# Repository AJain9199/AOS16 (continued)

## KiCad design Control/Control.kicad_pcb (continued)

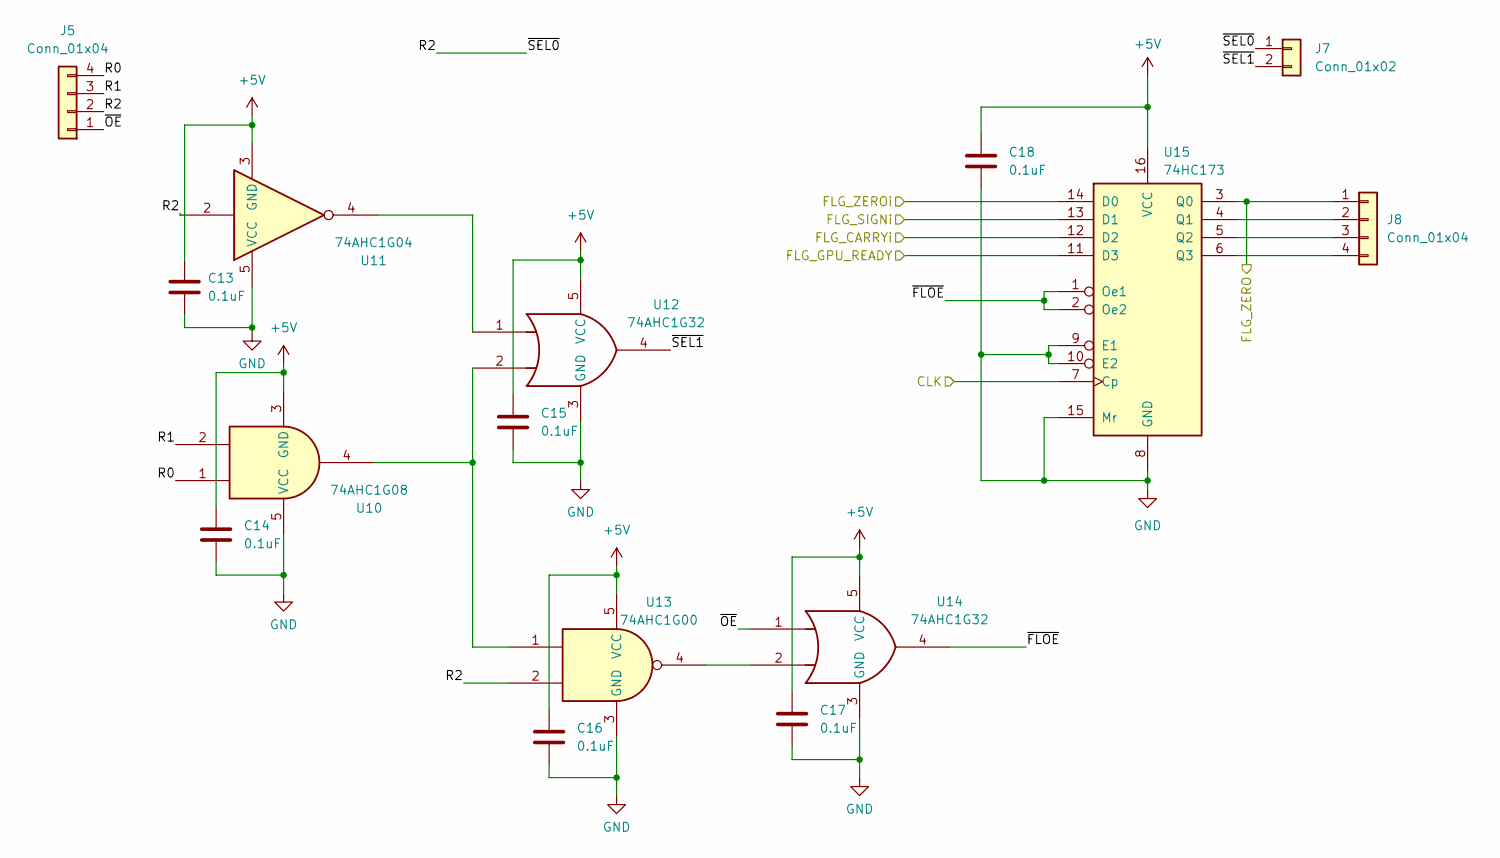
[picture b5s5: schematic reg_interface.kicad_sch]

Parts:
C13, C14, C15, C16, C17, C18: 0.1uF; C_0603_1608Metric
J5, J8: Conn_01x04; PinSocket_1x04_P2.54mm_Vertical
J7: Conn_01x02; PinHeader_1x02_P2.54mm_Vertical
U10: 74AHC1G08; SOT-23-5
U11: 74AHC1G04; SOT-23-5
U12, U14: 74AHC1G32; SOT-23-5
U13: 74AHC1G00; SOT-23-5
U15: 74HC173; SOIC-16_3.9x9.9mm_P1.27mm

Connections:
+5V: C13.1, C14.1, C15.1, C16.1, C17.1, C18.1, U10.3 (GND), U11.3 (GND), U12.5 (VCC), U13.5 (VCC), U14.5 (VCC), U15.16 (VCC); also elsewhere on the board
/ALU interface/FLG_CARRYo: U15.12 (D2); also elsewhere on the board
/ALU interface/FLG_SIGNo: U15.13 (D1); also elsewhere on the board
/ALU interface/FLG_ZEROo: U15.14 (D0); also elsewhere on the board
/CLK: U15.7 (Cp); also elsewhere on the board
/FLG_ZERO: J8.1, U15.3 (Q0); also elsewhere on the board
/register interface/FLG_GPU_READY: U15.11 (D3); also elsewhere on the board
/register interface/R0: J5.4, U10.1
/register interface/R1: J5.3, U10.2
/register interface/R2: J5.2, J7.1, U11.2, U13.2
/register interface/~FLOE: U14.4, U15.1 (Oe1), U15.2 (Oe2)
/register interface/~OE: J5.1, U14.1
/register interface/~SEL1: J7.2, U12.4
GND: C13.2, C14.2, C15.2, C16.2, C17.2, C18.2, U10.5 (VCC), U11.5 (VCC), U12.3 (GND), U13.3 (GND), U14.3 (GND), U15.8 (GND), U15.9 (E1), U15.10 (E2), U15.15 (Mr); also elsewhere on the board
unnamed: J8.2, U15.4 (Q1)
unnamed: J8.3, U15.5 (Q2)
unnamed: J8.4, U15.6 (Q3)
unnamed: U10.4, U12.2, U13.1
unnamed: U11.4, U12.1
unnamed: U13.4, U14.2

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
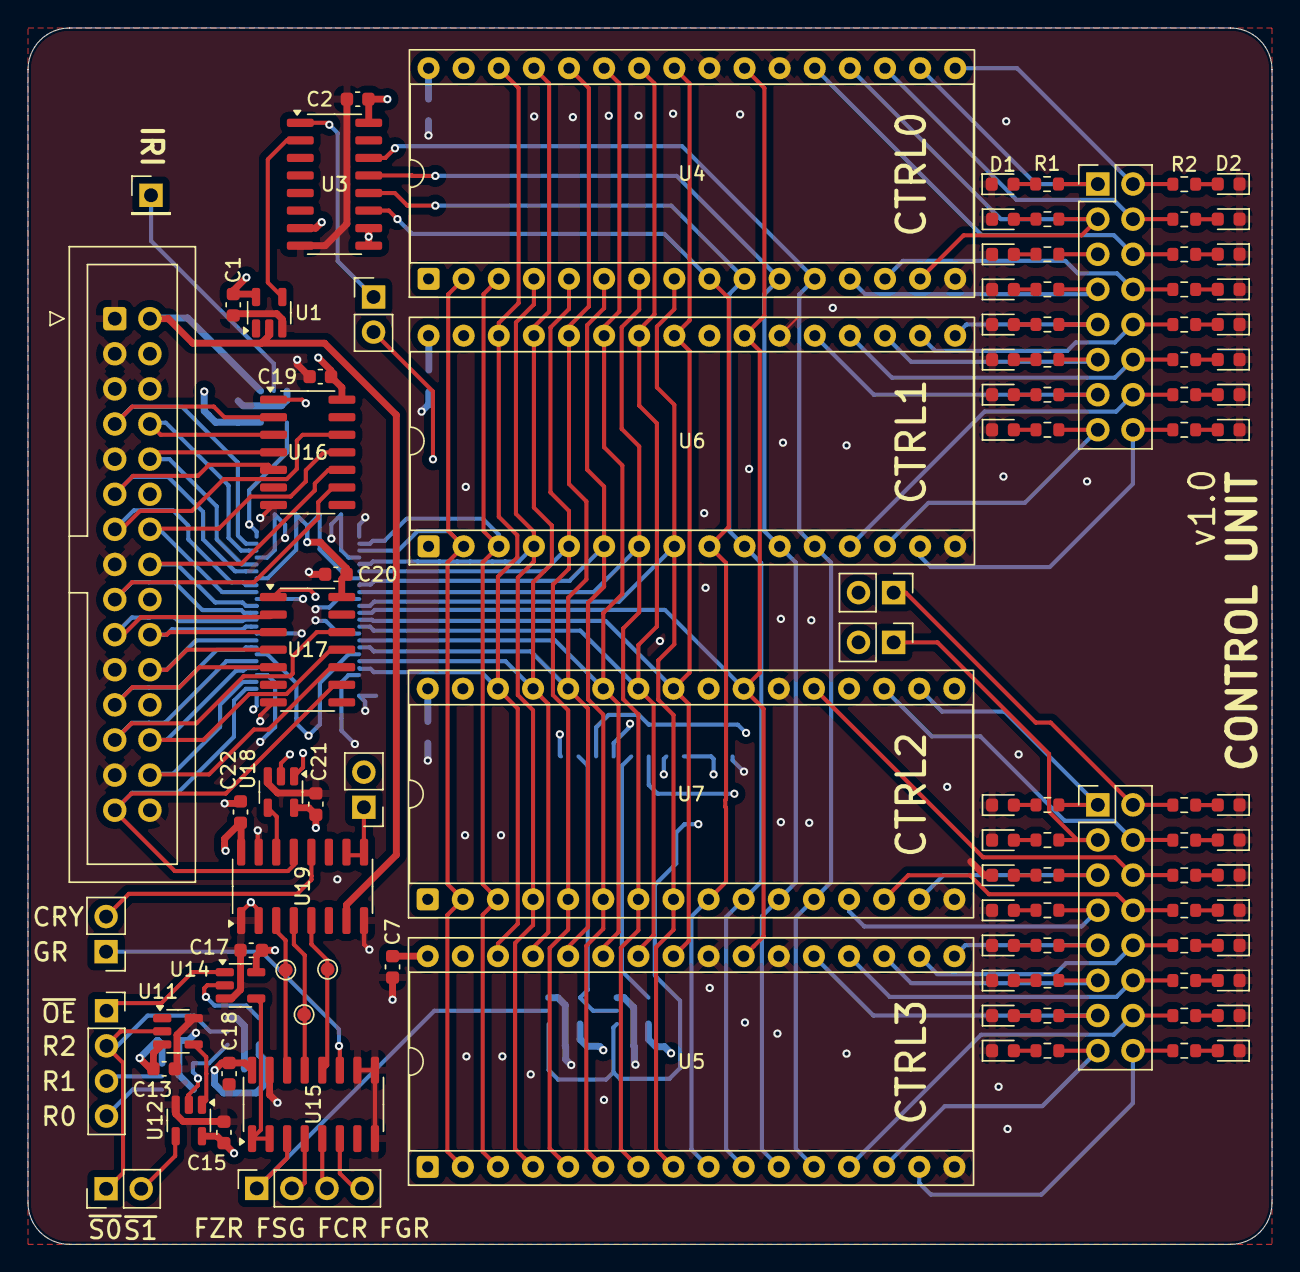
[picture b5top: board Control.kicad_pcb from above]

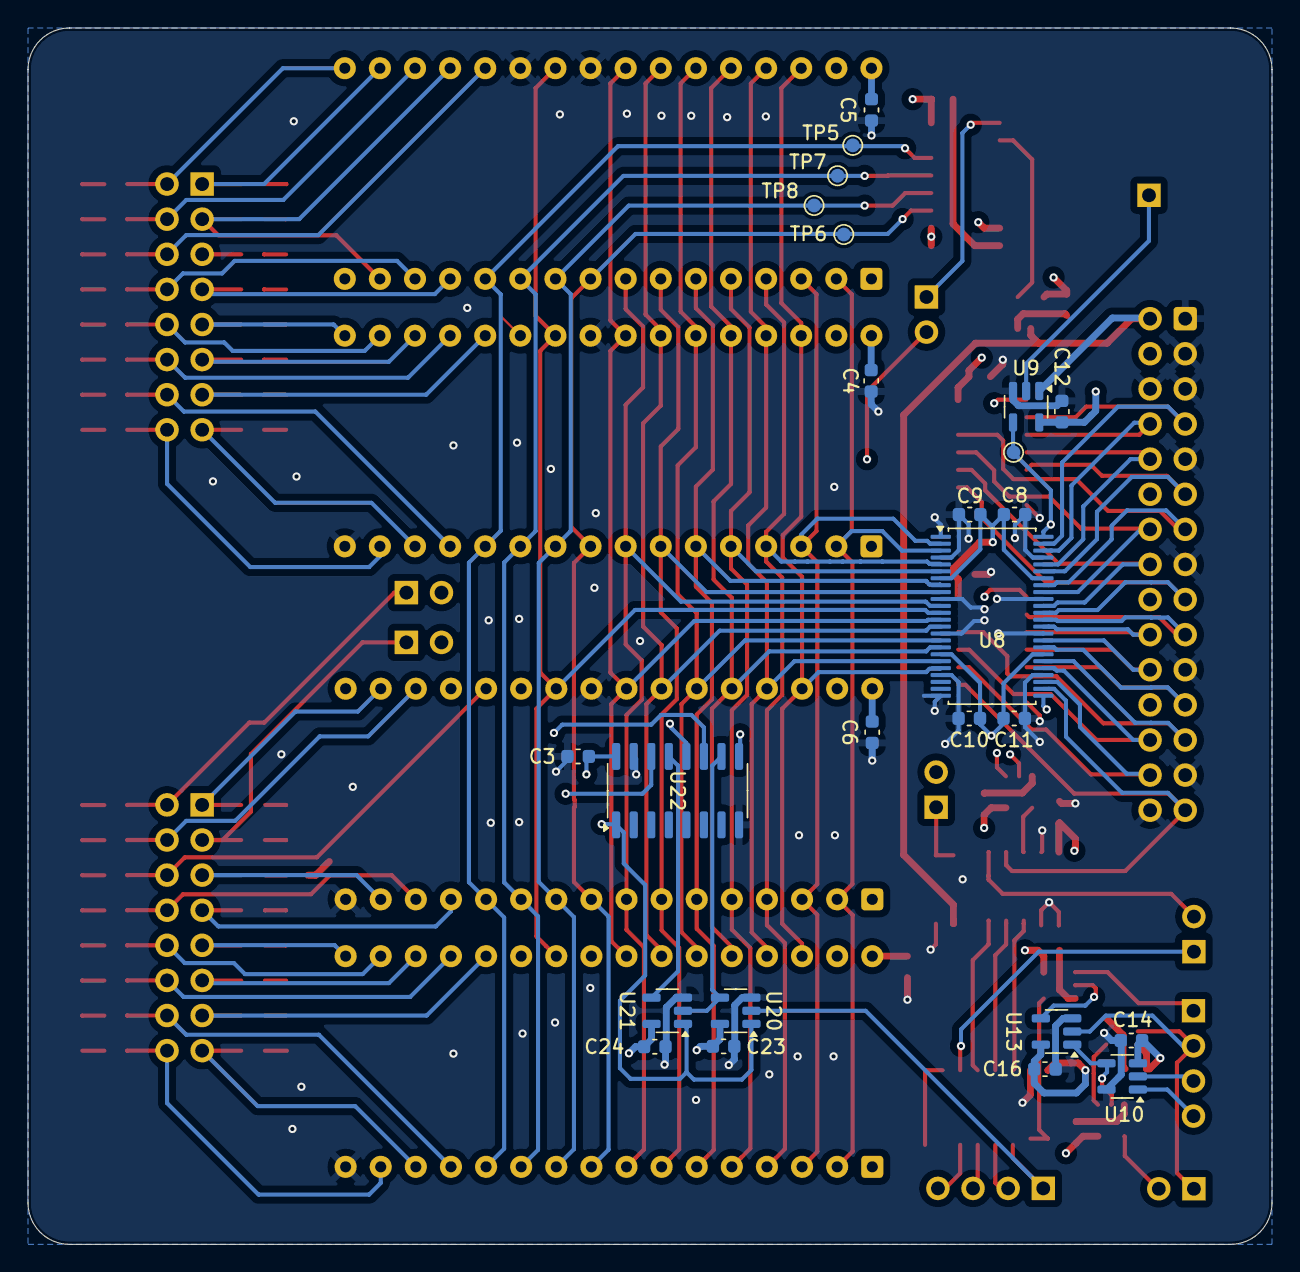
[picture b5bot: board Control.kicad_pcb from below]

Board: 4 copper layers, 90.0 x 88.0 mm, 129 parts (25 on the bottom side), 133 nets.

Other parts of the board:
C8, C9, C10, C11: 0.01uF; C_0603_1608Metric
C12: 0.1uF; C_0603_1608Metric
J3: Conn_02x15_Odd_Even; IDC-Header_2x15_P2.54mm_Vertical
TP1: TestPoint; TestPoint_Pad_D1.0mm
U8: SN74AHCT16374DGGR; TSSOP-48_6.1x12.5mm_P0.5mm
U9: 74AHC1G08; SOT-23-5

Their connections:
+5V: C8.1, C9.1, C10.1, C11.1, C12.1, J3.4, U8.7 (VCC_1), U8.18 (VCC_2), U8.31 (VCC), U8.42 (VCC_4), U9.5 (VCC); also elsewhere on the board
/ALU interface/BUS0: J3.7, U8.47 (1D1); also elsewhere on the board
/ALU interface/BUS1: J3.8, U8.46 (1D2); also elsewhere on the board
/ALU interface/BUS2: J3.10, U8.44 (1D3); also elsewhere on the board
/ALU interface/BUS3: J3.11, U8.43 (1D4); also elsewhere on the board
/ALU interface/BUS4: J3.13, U8.41 (1D5); also elsewhere on the board
/ALU interface/BUS5: J3.14, U8.40 (1D6); also elsewhere on the board
/ALU interface/BUS6: J3.16, U8.38 (1D7); also elsewhere on the board
/ALU interface/BUS7: J3.17, U8.37 (1D8); also elsewhere on the board
/ALU interface/BUS8: J3.19, U8.36 (2D1); also elsewhere on the board
/ALU interface/BUS9: J3.20, U8.35 (2D2); also elsewhere on the board
/ALU interface/BUS10: J3.22, U8.33 (2D3); also elsewhere on the board
/ALU interface/BUS11: J3.23, U8.32 (2D4); also elsewhere on the board
/ALU interface/BUS12: J3.25, U8.30 (2D5); also elsewhere on the board
/ALU interface/BUS13: J3.26, U8.29 (2D6); also elsewhere on the board
/ALU interface/BUS14: J3.28, U8.27 (2D7); also elsewhere on the board
/ALU interface/BUS15: J3.29, U8.26 (2D8); also elsewhere on the board
/CLK: J3.2, U9.1; also elsewhere on the board
/reg16/DOUT0: U8.2 (1Q1); also elsewhere on the board
/reg16/DOUT1: U8.3 (1Q2); also elsewhere on the board
/reg16/DOUT2: U8.5 (1Q3); also elsewhere on the board
/reg16/DOUT3: U8.6 (1Q4); also elsewhere on the board
/reg16/DOUT4: U8.8 (1Q5); also elsewhere on the board
/reg16/DOUT5: U8.9 (1Q6); also elsewhere on the board
/reg16/DOUT6: U8.11 (1Q7); also elsewhere on the board
/reg16/DOUT7: U8.12 (1Q8); also elsewhere on the board
/reg16/DOUT8: U8.13 (2Q1); also elsewhere on the board
/reg16/DOUT9: U8.14 (2Q2); also elsewhere on the board
/reg16/DOUT10: U8.16 (2Q3); also elsewhere on the board
/reg16/DOUT11: U8.17 (2Q4); also elsewhere on the board
/reg16/DOUT12: U8.19 (2Q5); also elsewhere on the board
/reg16/DOUT13: U8.20 (2Q6); also elsewhere on the board
/reg16/WE: U9.2; also elsewhere on the board
GND: C8.2, C9.2, C10.2, C11.2, C12.2, J3.1, J3.3, J3.5, J3.6, J3.9, J3.12, J3.15, J3.18, J3.21, J3.24, J3.27, J3.30, U8.1 (1~OE), U8.4 (GND_1), U8.10 (GND_2), U8.15 (GND_3), U8.21 (GND_4), U8.24 (2~OE), U8.28 (GND), U8.34 (GND_6), U8.39 (GND_7), U8.45 (GND_8), U9.3 (GND); also elsewhere on the board
unnamed: TP1.1, U8.25 (2CLK), U8.48 (1CLK), U9.4

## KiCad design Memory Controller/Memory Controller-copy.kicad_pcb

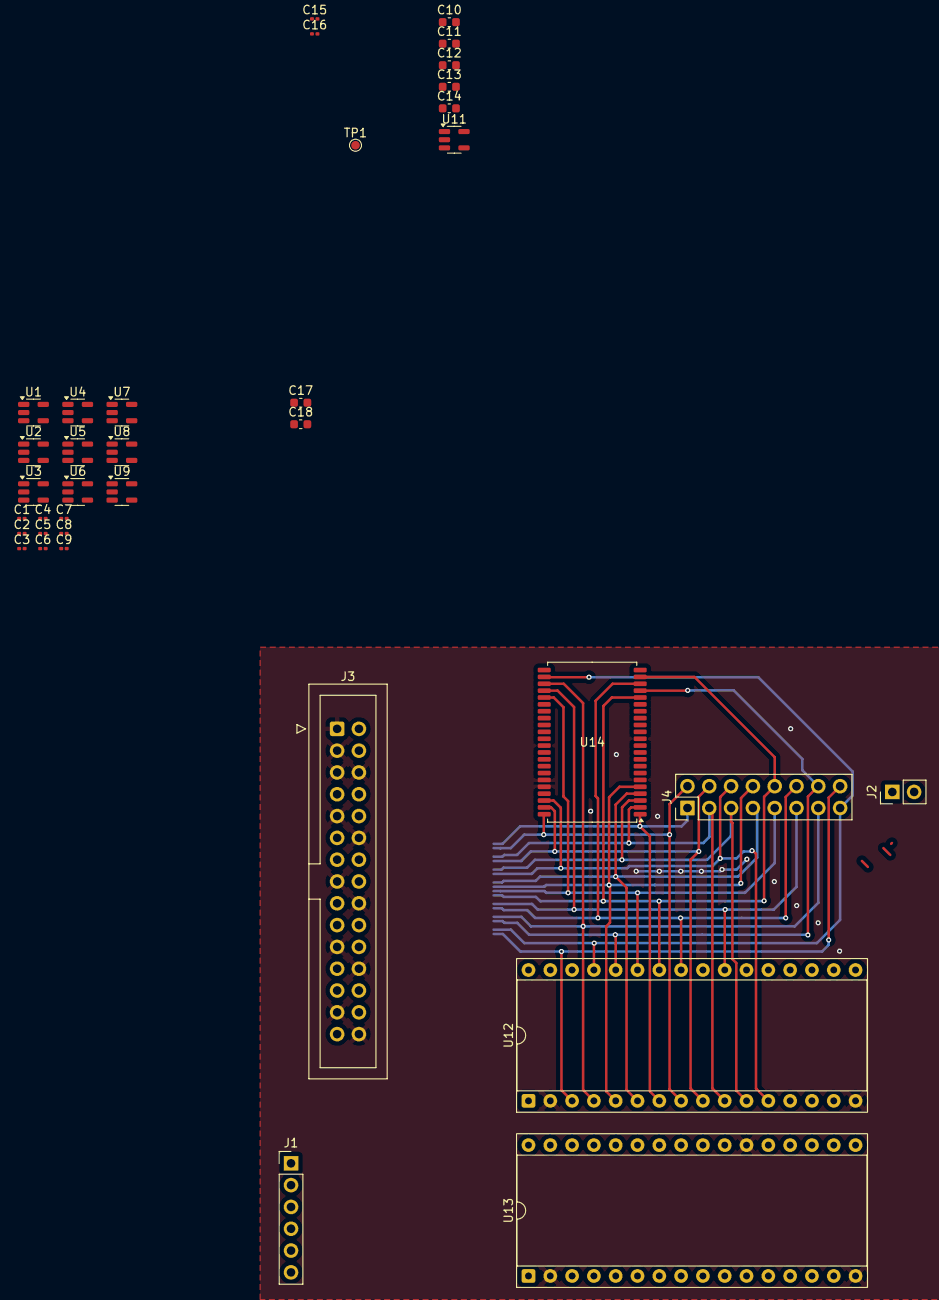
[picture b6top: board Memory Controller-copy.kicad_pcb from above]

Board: 2 copper layers, 37 parts (1 on the bottom side), 49 nets.

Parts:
C1, C2, C3, C4, C5, C6, C7, C8, C9, C15, C16: C; C_0201_0603Metric
C10, C11, C12, C13: 0.01uF; C_0603_1608Metric
C14, C17, C18: 0.1uF; C_0603_1608Metric
J1: Conn_01x06; PinHeader_1x06_P2.54mm_Vertical
J2: Conn_01x02; PinHeader_1x02_P2.54mm_Vertical
J3: Conn_02x15_Odd_Even; IDC-Header_2x15_P2.54mm_Vertical
J4: Conn_02x08_Top_Bottom; PinHeader_2x08_P2.54mm_Vertical
TP1: TestPoint; TestPoint_Pad_D1.0mm
U1, U3, U4, U5, U7, U8, U9: 74AHC1G32; SOT-23-5
U2, U6: 74AHC1G04; SOT-23-5
U10: SN74AHCT16374DGGR; TSSOP-48_6.1x12.5mm_P0.5mm
U11: 74AHC1G08; SOT-23-5
U12, U13: SST39SF010; DIP-32_W15.24mm_Socket
U14: 71016S12PHG8; TSOP-II-44_10.16x18.41mm_P0.8mm

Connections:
+5V: C1.1, C2.1, C3.1, C4.1, C5.1, C6.1, C7.1, C8.1, C9.1, C10.1, C11.1, C12.1, C13.1, C14.1, C15.1, C16.1, C17.1, C18.1, J3.4, U1.5 (VCC), U2.5 (VCC), U3.5 (VCC), U4.5 (VCC), U5.5 (VCC), U6.5 (VCC), U7.5 (VCC), U8.5 (VCC), U9.5 (VCC), U10.7 (VCC_1), U10.18 (VCC_2), U10.31 (VCC), U10.42 (VCC_4), U11.5 (VCC), U12.31 (PGM), U12.32 (VCC), U13.31 (PGM), U13.32 (VCC), U14.11 (VCC_1), U14.33 (VCC_2)
/BRE: J2.2, U8.4
/BWE: J2.1, U9.4
/CLK: J3.2, U11.1
/CRE: J1.5, U4.2, U5.1, U8.1
/CWE: J1.4, U3.1, U9.2
/MAL: J1.3, U11.2
/RAM_RE: U3.4, U14.41 (~OE)
/RAM_WE: U4.4, U14.17 (~WE)
/ROM_RE: U5.4, U12.24 (OE), U13.24 (OE)
/RSE: J1.2, U1.2, U2.2, U7.1
/bus_conn/IO0: J3.7, U10.47 (1D1)
/bus_conn/IO1: J3.8, U10.46 (1D2)
/bus_conn/IO2: J3.10, U10.44 (1D3)
/bus_conn/IO3: J3.11, U10.43 (1D4)
/bus_conn/IO4: J3.13, U10.41 (1D5)
/bus_conn/IO5: J3.14, U10.40 (1D6)
/bus_conn/IO6: J3.16, U10.38 (1D7)
/bus_conn/IO7: J3.17, U10.37 (1D8)
/bus_conn/IO8: J3.19, U10.36 (2D1)
/bus_conn/IO9: J3.20, U10.35 (2D2)
/bus_conn/IO10: J3.22, U10.33 (2D3)
/bus_conn/IO11: J3.23, U10.32 (2D4)
/bus_conn/IO12: J3.25, U10.30 (2D5)
/bus_conn/IO13: J3.26, U10.29 (2D6)
/bus_conn/IO14: J3.28, U10.27 (2D7)
/bus_conn/IO15: J3.29, U10.26 (2D8)
/word_conn/IN0: J4.1, U10.2 (1Q1), U12.7 (A5), U13.12 (A0), U14.1 (A4)
/word_conn/IN1: J4.2, U10.3 (1Q2), U12.8 (A4), U13.11 (A1), U14.44 (A5)
/word_conn/IN2: J4.3, U10.5 (1Q3), U12.10 (A2), U13.10 (A2), U14.2 (A3)
/word_conn/IN3: J4.4, U10.6 (1Q4), U12.9 (A3), U13.9 (A3), U14.43 (A6)
/word_conn/IN4: J4.5, U10.8 (1Q5), U12.11 (A1), U13.8 (A4), U14.3 (A2)
/word_conn/IN5: J4.6, U10.9 (1Q6), U12.12 (A0), U13.7 (A5), U14.42 (A7)
/word_conn/IN6: J4.7, U10.11 (1Q7), U12.6 (A6), U13.6 (A6), U14.4 (A1)
/word_conn/IN7: J4.8, U10.12 (1Q8), U12.5 (A7), U13.5 (A7), U14.5 (A0)
/word_conn/IN8: J4.9, U10.13 (2Q1), U12.27 (A8), U13.27 (A8), U14.27 (A8)
/word_conn/IN9: J4.10, U10.14 (2Q2), U12.26 (A9), U13.26 (A9), U14.18 (A15), U14.21 (A12)
/word_conn/IN10: J4.11, U10.16 (2Q3), U12.23 (A10), U13.23 (A10), U14.26 (A9)
/word_conn/IN11: J4.12, U10.17 (2Q4), U12.25 (A11), U13.25 (A11), U14.20 (A13)
/word_conn/IN12: J4.13, U10.19 (2Q5), U12.4 (A12), U13.4 (A12), U14.25 (A10)
/word_conn/IN13: J4.14, U10.20 (2Q6), U12.28 (A13), U13.28 (A13), U14.19 (A14)
/word_conn/IN14: J4.15, U10.22 (2Q7), U12.29 (A14), U13.29 (A14), U14.24 (A11)
/word_conn/IN15: J4.16, U1.1, U6.2, U10.23 (2Q8), U12.3 (A15), U13.3 (A15)
GND: C1.2, C2.2, C3.2, C4.2, C5.2, C6.2, C7.2, C8.2, C9.2, C10.2, C11.2, C12.2, C13.2, C14.2, C15.2, C16.2, C17.2, C18.2, J3.1, J3.3, J3.5, J3.6, J3.9, J3.12, J3.15, J3.18, J3.21, J3.24, J3.27, J3.30, U1.3 (GND), U2.3 (GND), U3.3 (GND), U4.3 (GND), U5.3 (GND), U6.3 (GND), U7.3 (GND), U8.3 (GND), U9.3 (GND), U10.1 (1~OE), U10.4 (GND_1), U10.10 (GND_2), U10.15 (GND_3), U10.21 (GND_4), U10.24 (2~OE), U10.28 (GND), U10.34 (GND_6), U10.39 (GND_7), U10.45 (GND_8), U11.3 (GND), U12.2 (A16), U12.16 (GND), U12.22 (CE), U13.2 (A16), U13.16 (GND), U13.22 (CE), U14.6 (~CS), U14.12 (VSS_1), U14.34 (VSS_2), U14.39 (~BLE), U14.40 (~BHE)
unnamed: U1.4, U3.2, U4.1
unnamed: U2.4, U5.2
unnamed: U6.4, U7.2
unnamed: U7.4, U8.2, U9.1
unnamed: TP1.1, U10.25 (2CLK), U10.48 (1CLK), U11.4

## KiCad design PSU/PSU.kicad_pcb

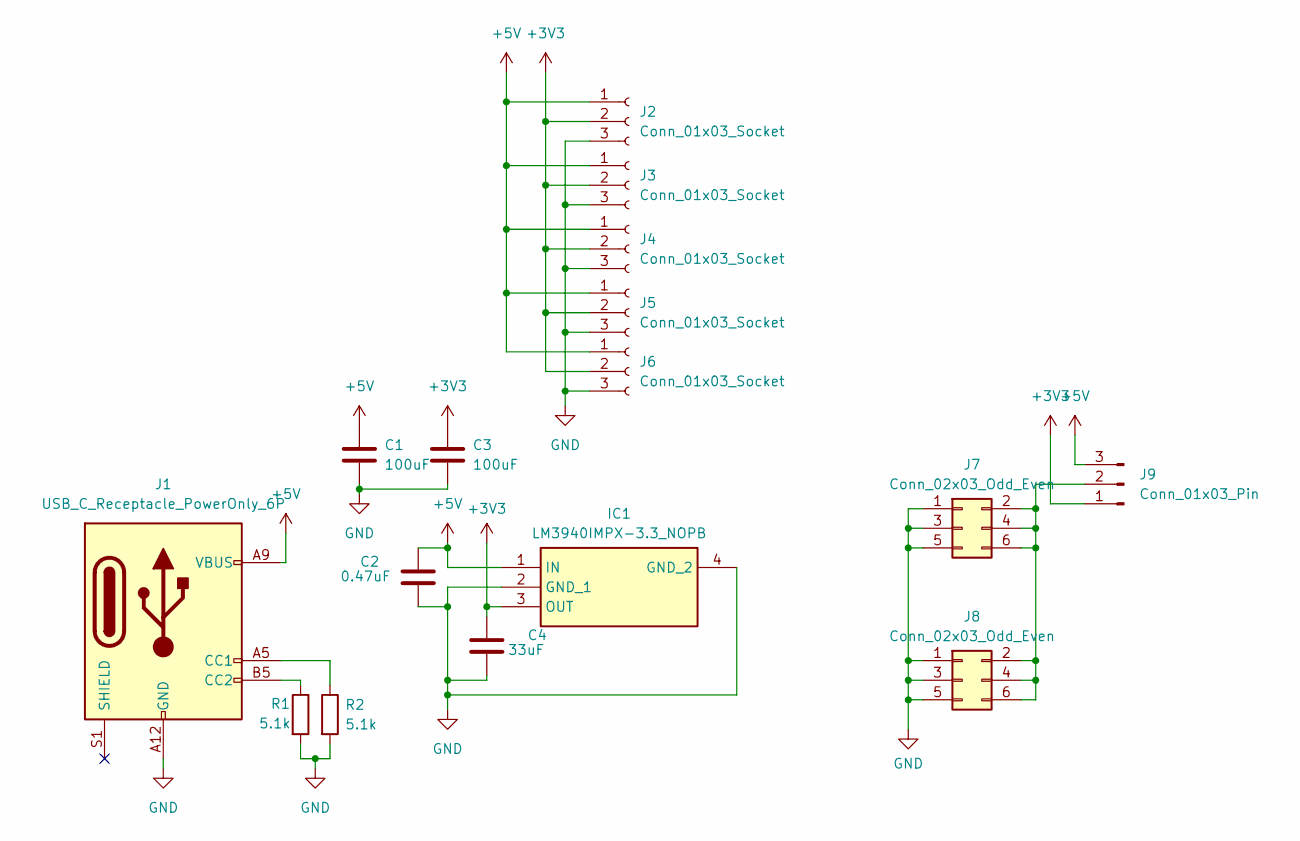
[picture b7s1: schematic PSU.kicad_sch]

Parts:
C1, C3: 100uF; CP_Elec_5x5.3
C2: 0.47uF; C_0603_1608Metric
C4: 33uF; C_0603_1608Metric
IC1: LM3940IMPX-3.3_NOPB; SOT-223; Mouser Part Number 926-LM3940IMPX33NOPB
J1: USB_C_Receptacle_PowerOnly_6P; USB_C_Receptacle_GCT_USB4125-xx-x-0190_6P_TopMnt_Horizontal
J2, J3, J4, J5, J6: Conn_01x03_Socket; JST_EH_B3B-EH-A_1x03_P2.50mm_Vertical
J7, J8: Conn_02x03_Odd_Even; PinHeader_2x03_P2.54mm_Vertical
J9: Conn_01x03_Pin; PinHeader_1x03_P2.54mm_Vertical
R1, R2: 5.1k; R_0603_1608Metric

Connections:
+3V3: C3.1, C4.1, IC1.3 (OUT), J2.2, J3.2, J4.2, J5.2, J6.2, J9.1
+5V: C1.1, C2.1, IC1.1 (IN), J1.A9 (VBUS), J1.B9 (VBUS), J2.1, J3.1, J4.1, J5.1, J6.1, J9.3
GND: C1.2, C2.2, C3.2, C4.2, IC1.2 (GND_1), IC1.4 (GND_2), J1.A12 (GND), J1.B12 (GND), J2.3, J3.3, J4.3, J5.3, J6.3, J7.1, J7.3, J7.5, J8.1, J8.3, J8.5, R1.2, R2.2
unnamed: J1.A5 (CC1), R2.1
unnamed: J1.B5 (CC2), R1.1
unnamed: J7.2, J7.4, J7.6, J8.2, J8.4, J8.6, J9.2

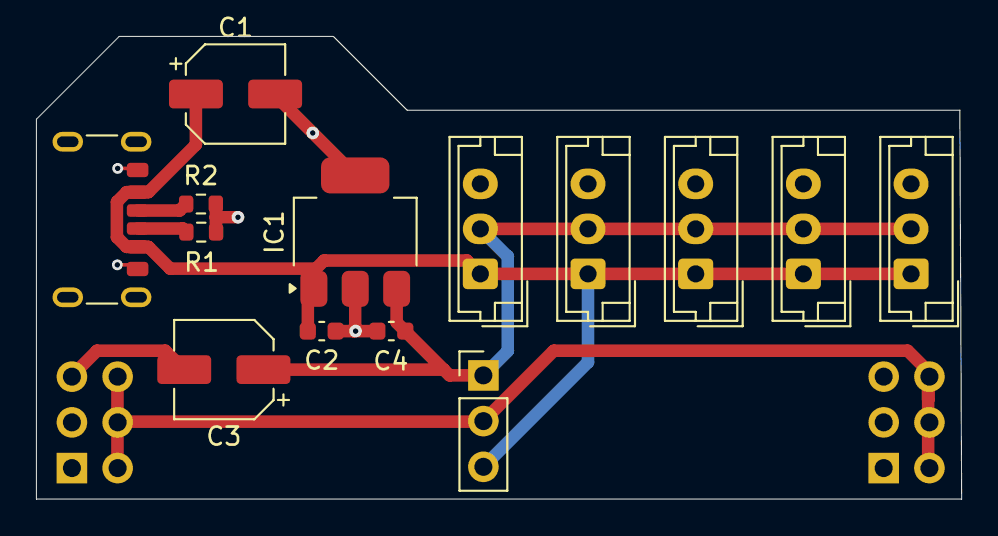
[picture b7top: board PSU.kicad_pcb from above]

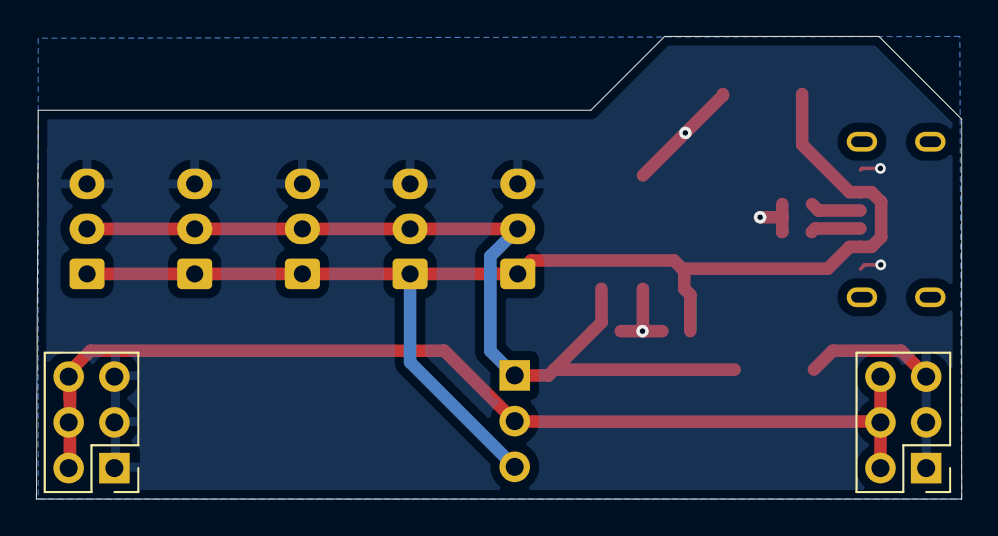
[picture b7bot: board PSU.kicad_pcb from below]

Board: 2 copper layers, 51.4 x 25.7 mm, 16 parts (2 on the bottom side), 6 nets.

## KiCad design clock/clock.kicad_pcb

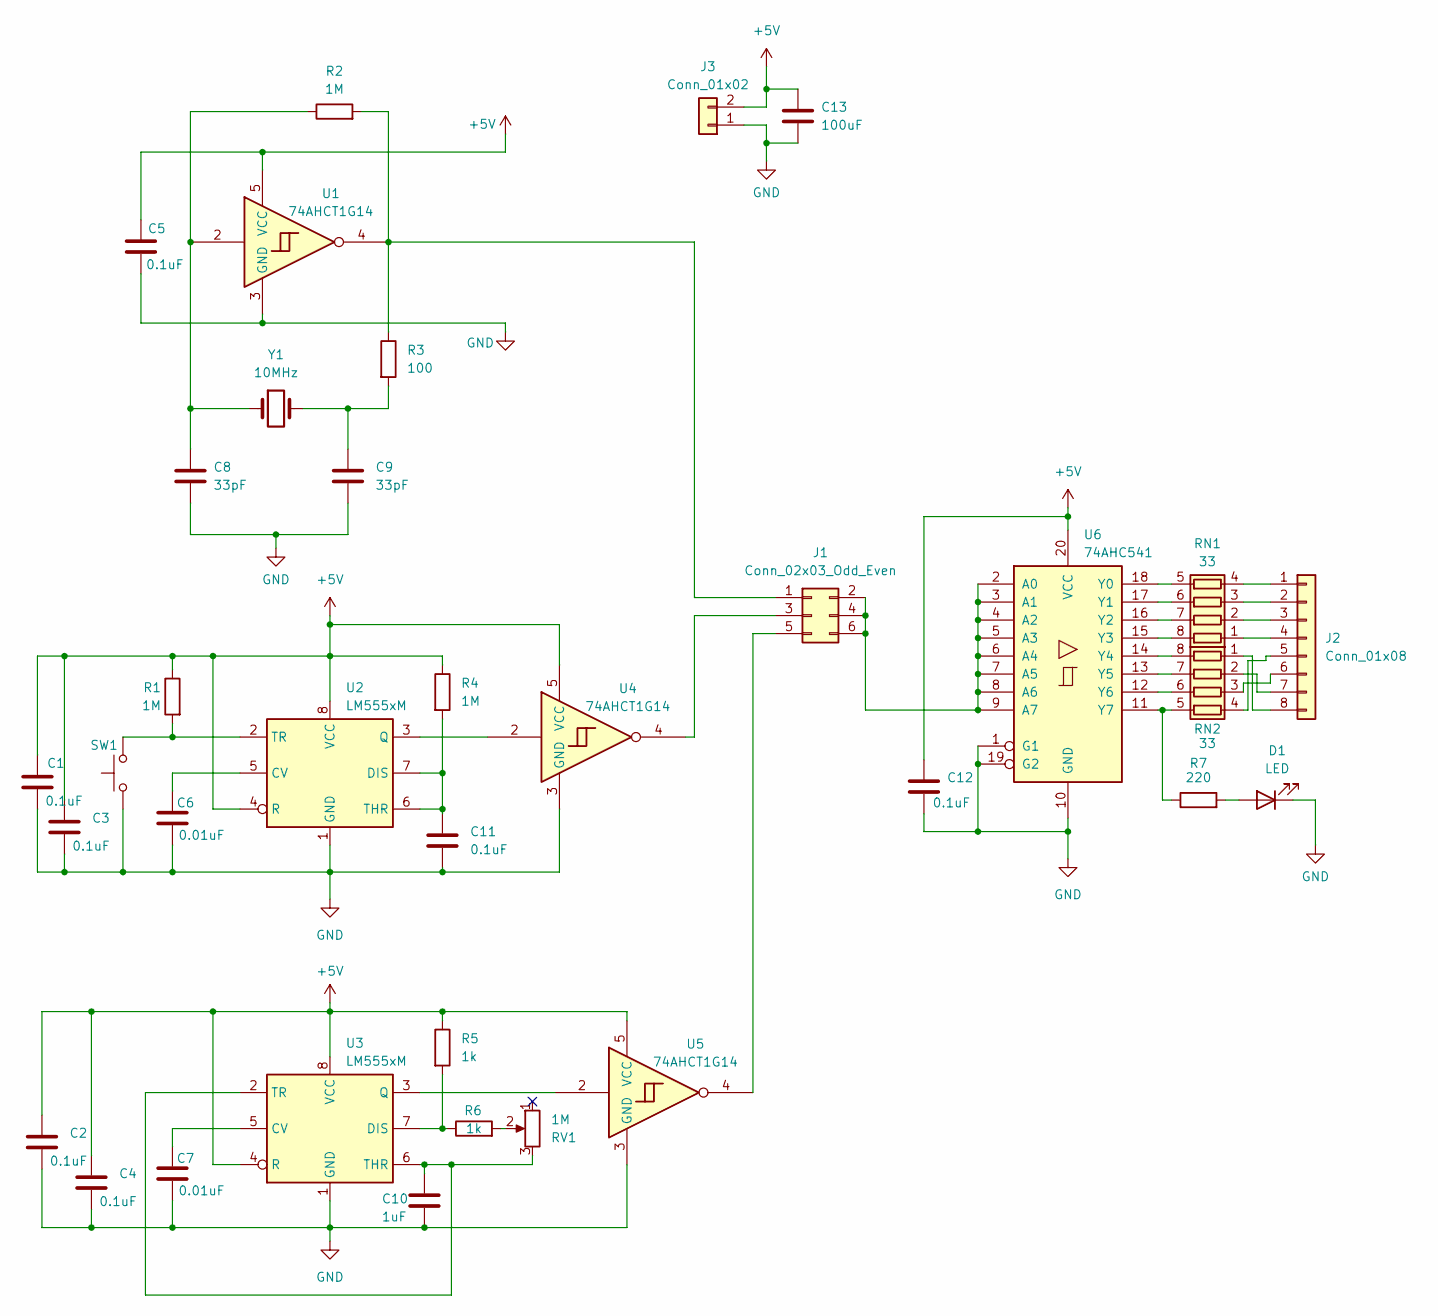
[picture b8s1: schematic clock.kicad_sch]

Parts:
C1, C2, C3, C4, C5, C11, C12: 0.1uF; C_0603_1608Metric
C6, C7: 0.01uF; C_0603_1608Metric
C8, C9: 33pF; C_0603_1608Metric
C10: 1uF; C_0603_1608Metric
C13: 100uF; CP_Elec_5x5.3
D1: LED; LED_0603_1608Metric
J1: Conn_02x03_Odd_Even; PinHeader_2x03_P2.54mm_Vertical
J2: Conn_01x08; PinHeader_1x08_P2.54mm_Vertical
J3: Conn_01x02; PinHeader_1x02_P2.54mm_Vertical
R1, R2, R4: 1M; R_0603_1608Metric
R3: 100; R_0603_1608Metric
R5, R6: 1k; R_0603_1608Metric
R7: 220; R_0603_1608Metric
RN1, RN2: 33; R_Array_Convex_4x1206
RV1: 1M; Potentiometer_Piher_PT-6-V_Vertical
SW1: SW_Push; SW_PUSH_6mm
U1, U4, U5: 74AHCT1G14; SOT-23-5
U2, U3: LM555xM; SOIC-8_3.9x4.9mm_P1.27mm
U6: 74AHC541; TSSOP-20_4.4x6.5mm_P0.65mm
Y1: 10MHz; Crystal_HC49-U_Vertical

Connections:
+5V: C1.1, C2.1, C3.1, C4.1, C5.1, C12.1, C13.1, J3.2, R1.1, R4.1, R5.1, U1.5 (VCC), U2.4 (R), U2.8 (VCC), U3.4 (R), U3.8 (VCC), U4.5 (VCC), U5.5 (VCC), U6.20 (VCC)
GND: C1.2, C2.2, C3.2, C4.2, C5.2, C6.2, C7.2, C8.2, C9.2, C10.2, C11.2, C12.2, C13.2, D1.1 (K), J3.1, SW1.1, U1.3 (GND), U2.1 (GND), U3.1 (GND), U4.3 (GND), U5.3 (GND), U6.1 (G1), U6.10 (GND), U6.19 (G2)
unnamed: C8.1, R2.1, U1.2, Y1.1
unnamed: C9.1, R3.2, Y1.2
unnamed: D1.2 (A), R7.2
unnamed: J1.1, R2.2, R3.1, U1.4
unnamed: J1.2, J1.4, J1.6, U6.2 (A0), U6.3 (A1), U6.4 (A2), U6.5 (A3), U6.6 (A4), U6.7 (A5), U6.8 (A6), U6.9 (A7)
unnamed: J1.3, U4.4
unnamed: J1.5, U5.4
unnamed: J2.1, RN1.4 (R4.1)
unnamed: J2.2, RN1.3 (R3.1)
unnamed: J2.3, RN1.2 (R2.1)
unnamed: J2.4, RN1.1 (R1.1)
unnamed: J2.5, RN2.4 (R4.1)
unnamed: J2.6, RN2.3 (R3.1)
unnamed: J2.7, RN2.2 (R2.1)
unnamed: J2.8, RN2.1 (R1.1)
unnamed: R6.2, RV1.2
unnamed: RN1.8 (R1.2), U6.15 (Y3)
unnamed: RN1.7 (R2.2), U6.16 (Y2)
unnamed: RN1.6 (R3.2), U6.17 (Y1)
unnamed: RN1.5 (R4.2), U6.18 (Y0)
unnamed: RN2.8 (R1.2), U6.14 (Y4)
unnamed: RN2.7 (R2.2), U6.13 (Y5)
unnamed: RN2.6 (R3.2), U6.12 (Y6)
unnamed: R7.1, RN2.5 (R4.2), U6.11 (Y7)
unnamed: C6.1, U2.5 (CV)
unnamed: C11.1, R4.2, U2.6 (THR), U2.7 (DIS)
unnamed: U2.3 (Q), U4.2
unnamed: R1.2, SW1.2, U2.2 (TR)
unnamed: C7.1, U3.5 (CV)
unnamed: R5.2, R6.1, U3.7 (DIS)
unnamed: U3.3 (Q), U5.2
unnamed: C10.1, RV1.3, U3.2 (TR), U3.6 (THR)

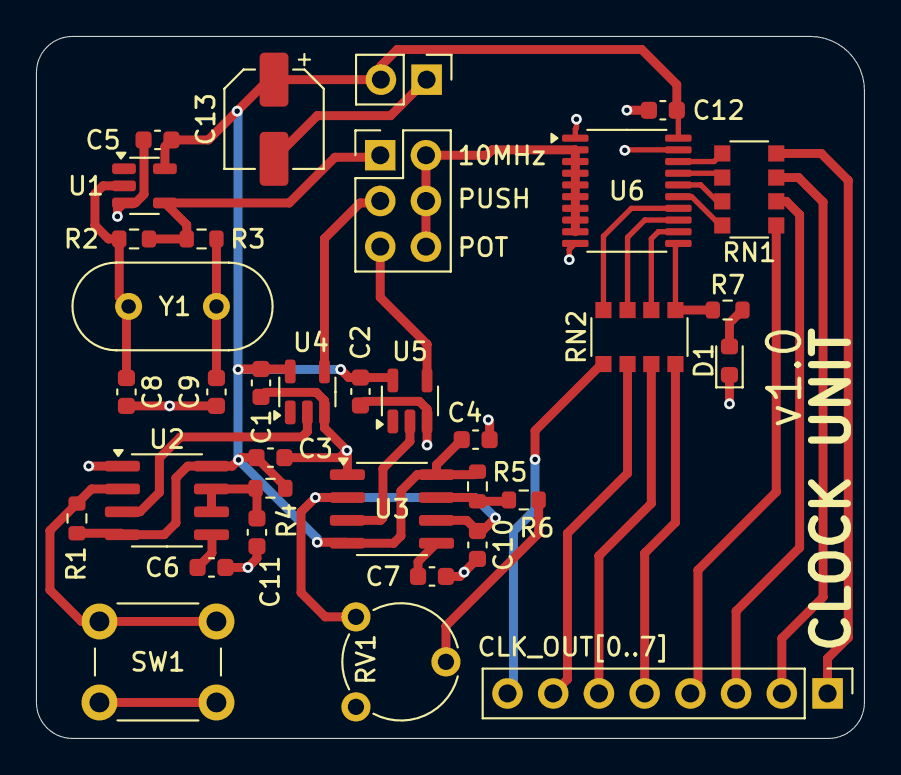
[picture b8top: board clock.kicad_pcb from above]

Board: 2 copper layers, 46.0 x 39.0 mm, 35 parts (0 on the bottom side), 34 nets.
